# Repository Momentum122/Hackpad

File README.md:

# SmolPad 

SmolPad is an open-source, custom 3x3 mechanical macropad powered by the Seeed Studio XIAO RP2040 microcontroller. It features a 3x3 diode key matrix, an EC11 rotary encoder for volume control, and a 0.91" I2C OLED display for a plain text output (for now) , all housed in a custom 3D-printed case running KMK Firmware .

# Features

 **3x3 Key Matrix:** Direct-soldered MX mechanical switches with 1N4148 diodes .
 **EC11 Rotary Encoder:** Smooth volume adjustment and press-to-mute functionality.
 **0.91" I2C OLED Display:** 128x32 resolution driven by the SSD1306 display controller displaying status information.
 **Compact Case Design:** Custom 2-piece case secured with M3 heat-set brass inserts.
 **Easy Customization:** Powered by KMK / CircuitPython—edit shortcuts on the fly by modifying `main.py` like a USB drive file.

Keymap
 Row 0 
  i) Media play/pause
  ii) Brightness Increase 
  iii) Brighness Decrease
 Row 1 
  i) Super/Windows key ( i know this one is weird but the one on my keyboard doesnt work so i will use this for the timebeing).
  ii) Audio Mute 
  iii) Copy ( Ctrl + C)
 Row 2
  i) Cut (ctrl + x)
  ii) Paste (ctrl + v)
  iii) undo (ctrl + z)

Rotary Encoder 
 i) Clockwise Turn - Volume Up
 ii) Counter-Clockwise - Volume Down
 iii) Push Switch Press - Mute Toggle ( will be later used to switch layers)

OLED Display 
i) currently Displays only a single static text i.e. Smolpad active 

All the Above can and will be most likely changed later on .

# Project Structure

HackPad
 CAD
  Top.step
  Top.stl
  Bottom.step
  Bottom.stl
  Hack Club Knurled Knob.step
 PCB
  smolpad.kicad_pcb
  smolpad.kicad_pro
  smolpad.kicad_sch
  smolpad.step
  gerbers(final).zip
 firmwarefiles
  boot.py
  kb.py
  main.py
  lib 
  kmk 
Imagaes
  Case
   Bottom.png
   Combined.png
   Top.png
  PCB 3d model.png
  Schematic.pdf
 BOM.csv
 README.md

NOTE :- PLEASE CHECK THE BOM.csv FOR THE MATERIALS

# Assembly instructions
PCB Fabrication: Upload production/gerbers/gerbers.zip to a PCB manufacturer (such as JLCPCB) with standard 1.6mm thickness and default settings.

3D Printing: Print the enclosure parts (smolpad_case_top.step and smolpad_case_bottom.step) .

Component Soldering: Solder the 1N4148 diodes onto the back of the pcb , ensuring correct polarity .
Solder the mechanical MX-style switches and the EC11 encoder 
Solder the Seeed Studio XIAO RP2040 microcontroller and the 0.91-inch OLED display
Enclosure Assembly: Mount the assembled PCB into the 3D-printed case using M3 screws.

# Firmware Flashing & Setup

The SmolPad runs on CircuitPython with KMK firmware using the Seeed Studio XIAO RP2040.
Enter Bootloader Mode: Connect the XIAO RP2040 to your computer via USB and double-tap the reset button. A drive named RPI-RP2 will appear.

Install CircuitPython Runtime: Drag and drop the official CircuitPython UF2 bootloader runtime onto the RPI-RP2 drive. The board will reboot and mount a new drive named CIRCUITPY.

Upload Firmware Files: Copy your firmware script files (main.py, kb.py, and the kmk/ library folder) directly into the root directory of the CIRCUITPY drive.

Test: The board will automatically execute main.py and initialize your keymap, rotary encoder, and OLED display.

 Acknowledgements :- i) Usage of Ai for understanding features of Kicad/Onshape , Usage of ai for guidance in few areas like firmware , Usage of ai for identifying errors and resolving them
 ii) All resources are not owned by me (except case and Pcb however you are free to use them if you want to).  
 iii) Created with the guidance of https://hackpad.hackclub.com/guide , https://youtu.be/8WXpGTIbxlQ?si=IzrQN_IX_nW7LFwR  .
 iv) Built with support from the Hack Club grants and resoureces —massive thanks to them for funding the hardware and making this project a reality.
 v) Built for Stardance hackclub 
 CONTACT INFO :- mandeepswami2010@gmail.com

Suggestions / Issues / Complaint(s) are accepted and appreciated for the betterment of the macropad.

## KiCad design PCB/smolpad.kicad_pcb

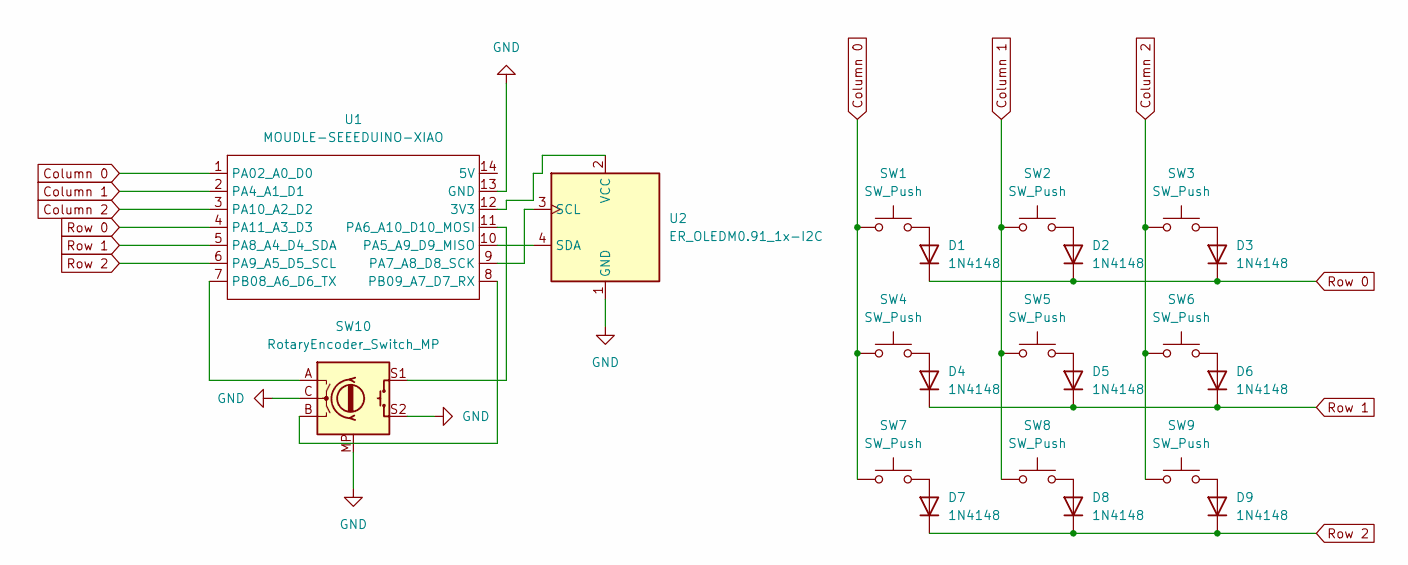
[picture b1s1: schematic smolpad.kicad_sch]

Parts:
D1, D2, D3, D4, D5, D6, D7, D8, D9: 1N4148; D_DO-35_SOD27_P7.62mm_Horizontal
SW1, SW2, SW3, SW4, SW5, SW6, SW7, SW8, SW9: SW_Push; SW_Cherry_MX_1.00u_PCB
SW10: RotaryEncoder_Switch_MP; RotaryEncoder_Alps_EC11E-Switch_Vertical_H20mm
U1: MOUDLE-SEEEDUINO-XIAO; XIAO-Generic-Hybrid-14P-2.54-21X17.8MM
U2: ER_OLEDM0.91_1x-I2C

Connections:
Column 0: SW1.1, SW4.1, SW7.1, U1.1 (PA02_A0_D0)
Column 1: SW2.1, SW5.1, SW8.1, U1.2 (PA4_A1_D1)
Column 2: SW3.1, SW6.1, SW9.1, U1.3 (PA10_A2_D2)
GND: SW10.C, SW10.MP, SW10.S2, U1.13 (GND), U2.1 (GND)
unnamed: D1.2 (A), SW1.2
unnamed: D2.2 (A), SW2.2
unnamed: D3.2 (A), SW3.2
unnamed: D4.2 (A), SW4.2
unnamed: D5.2 (A), SW5.2
unnamed: D6.2 (A), SW6.2
unnamed: D7.2 (A), SW7.2
unnamed: D8.2 (A), SW8.2
unnamed: D9.2 (A), SW9.2
unnamed: U1.12 (3V3), U2.2 (VCC)
unnamed: U1.10 (PA5_A9_D9_MISO), U2.4 (SDA)
unnamed: SW10.S1, U1.11 (PA6_A10_D10_MOSI)
unnamed: U1.9 (PA7_A8_D8_SCK), U2.3 (SCL)
unnamed: SW10.A, U1.7 (PB08_A6_D6_TX)
unnamed: SW10.B, U1.8 (PB09_A7_D7_RX)
Row 0: D1.1 (K), D2.1 (K), D3.1 (K), U1.4 (PA11_A3_D3)
Row 1: D4.1 (K), D5.1 (K), D6.1 (K), U1.5 (PA8_A4_D4_SDA)
Row 2: D7.1 (K), D8.1 (K), D9.1 (K), U1.6 (PA9_A5_D5_SCL)

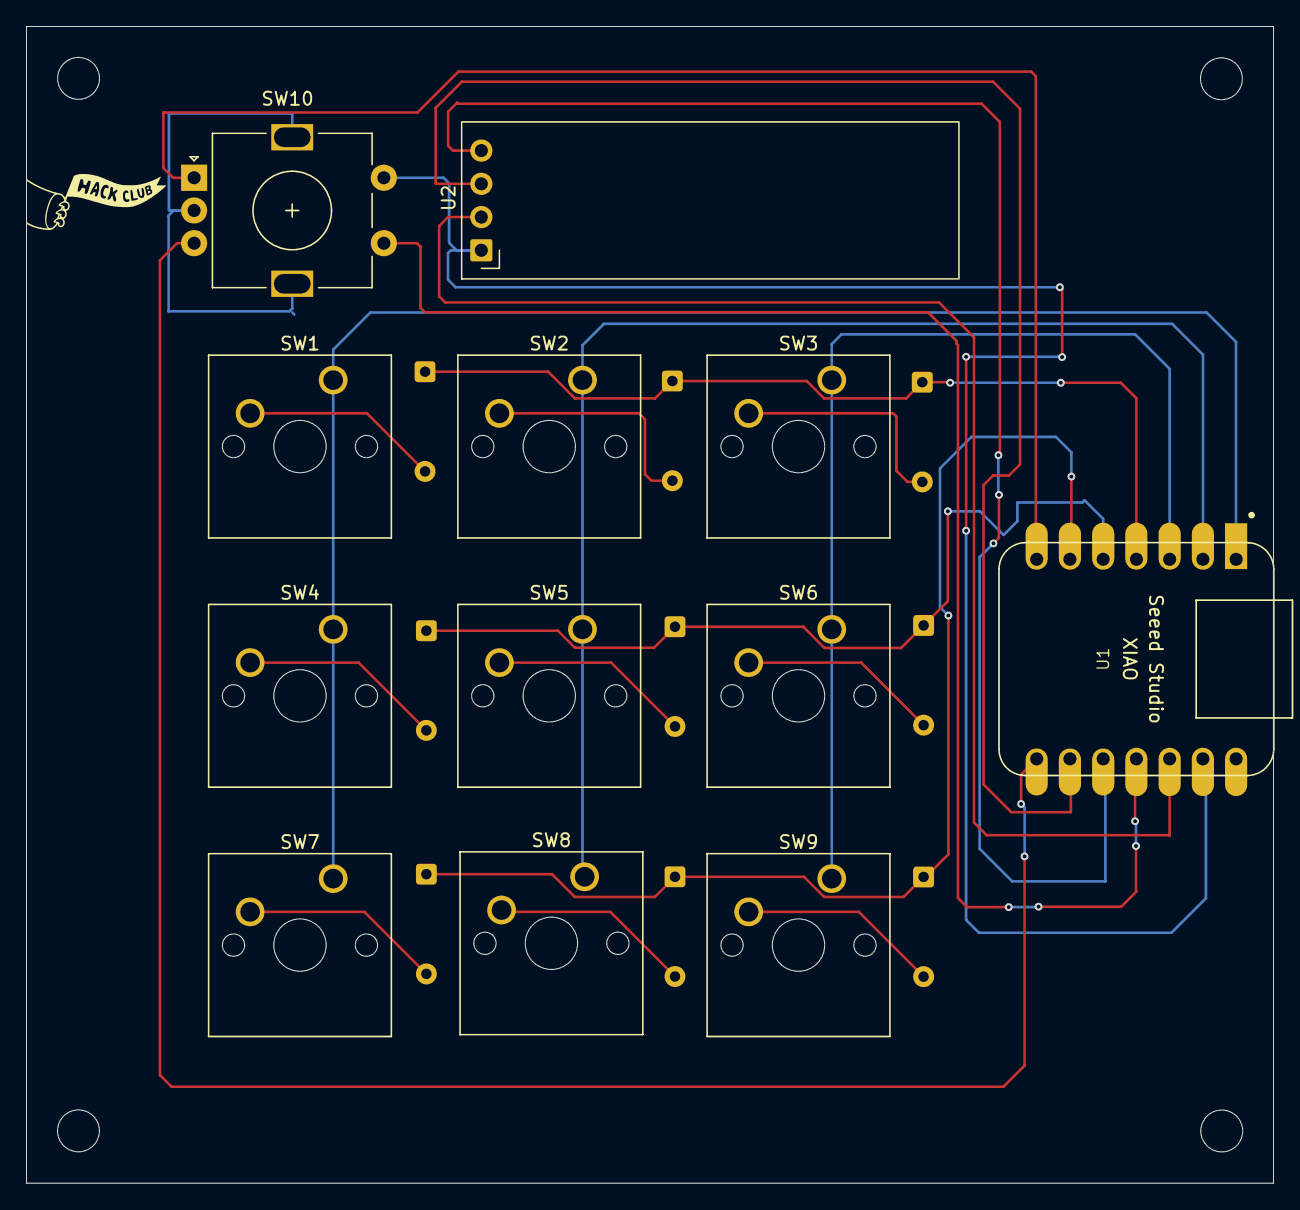
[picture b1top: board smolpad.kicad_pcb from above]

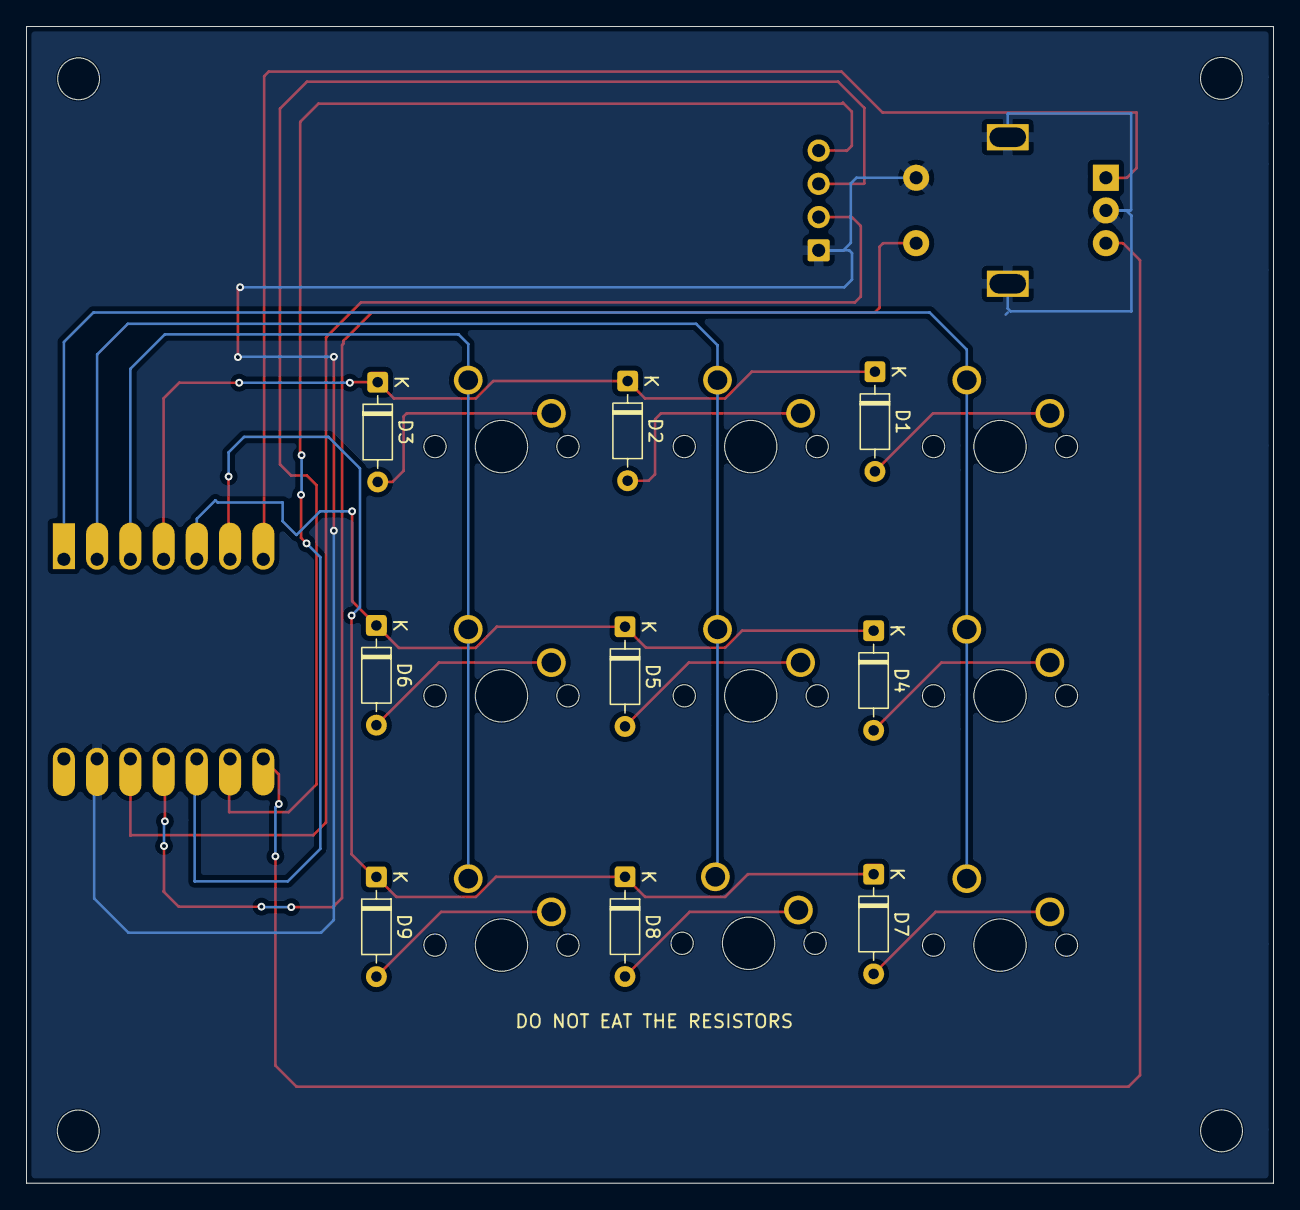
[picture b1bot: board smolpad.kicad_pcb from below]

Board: 2 copper layers, 95.3 x 88.4 mm, 21 parts (9 on the bottom side), 22 nets.
